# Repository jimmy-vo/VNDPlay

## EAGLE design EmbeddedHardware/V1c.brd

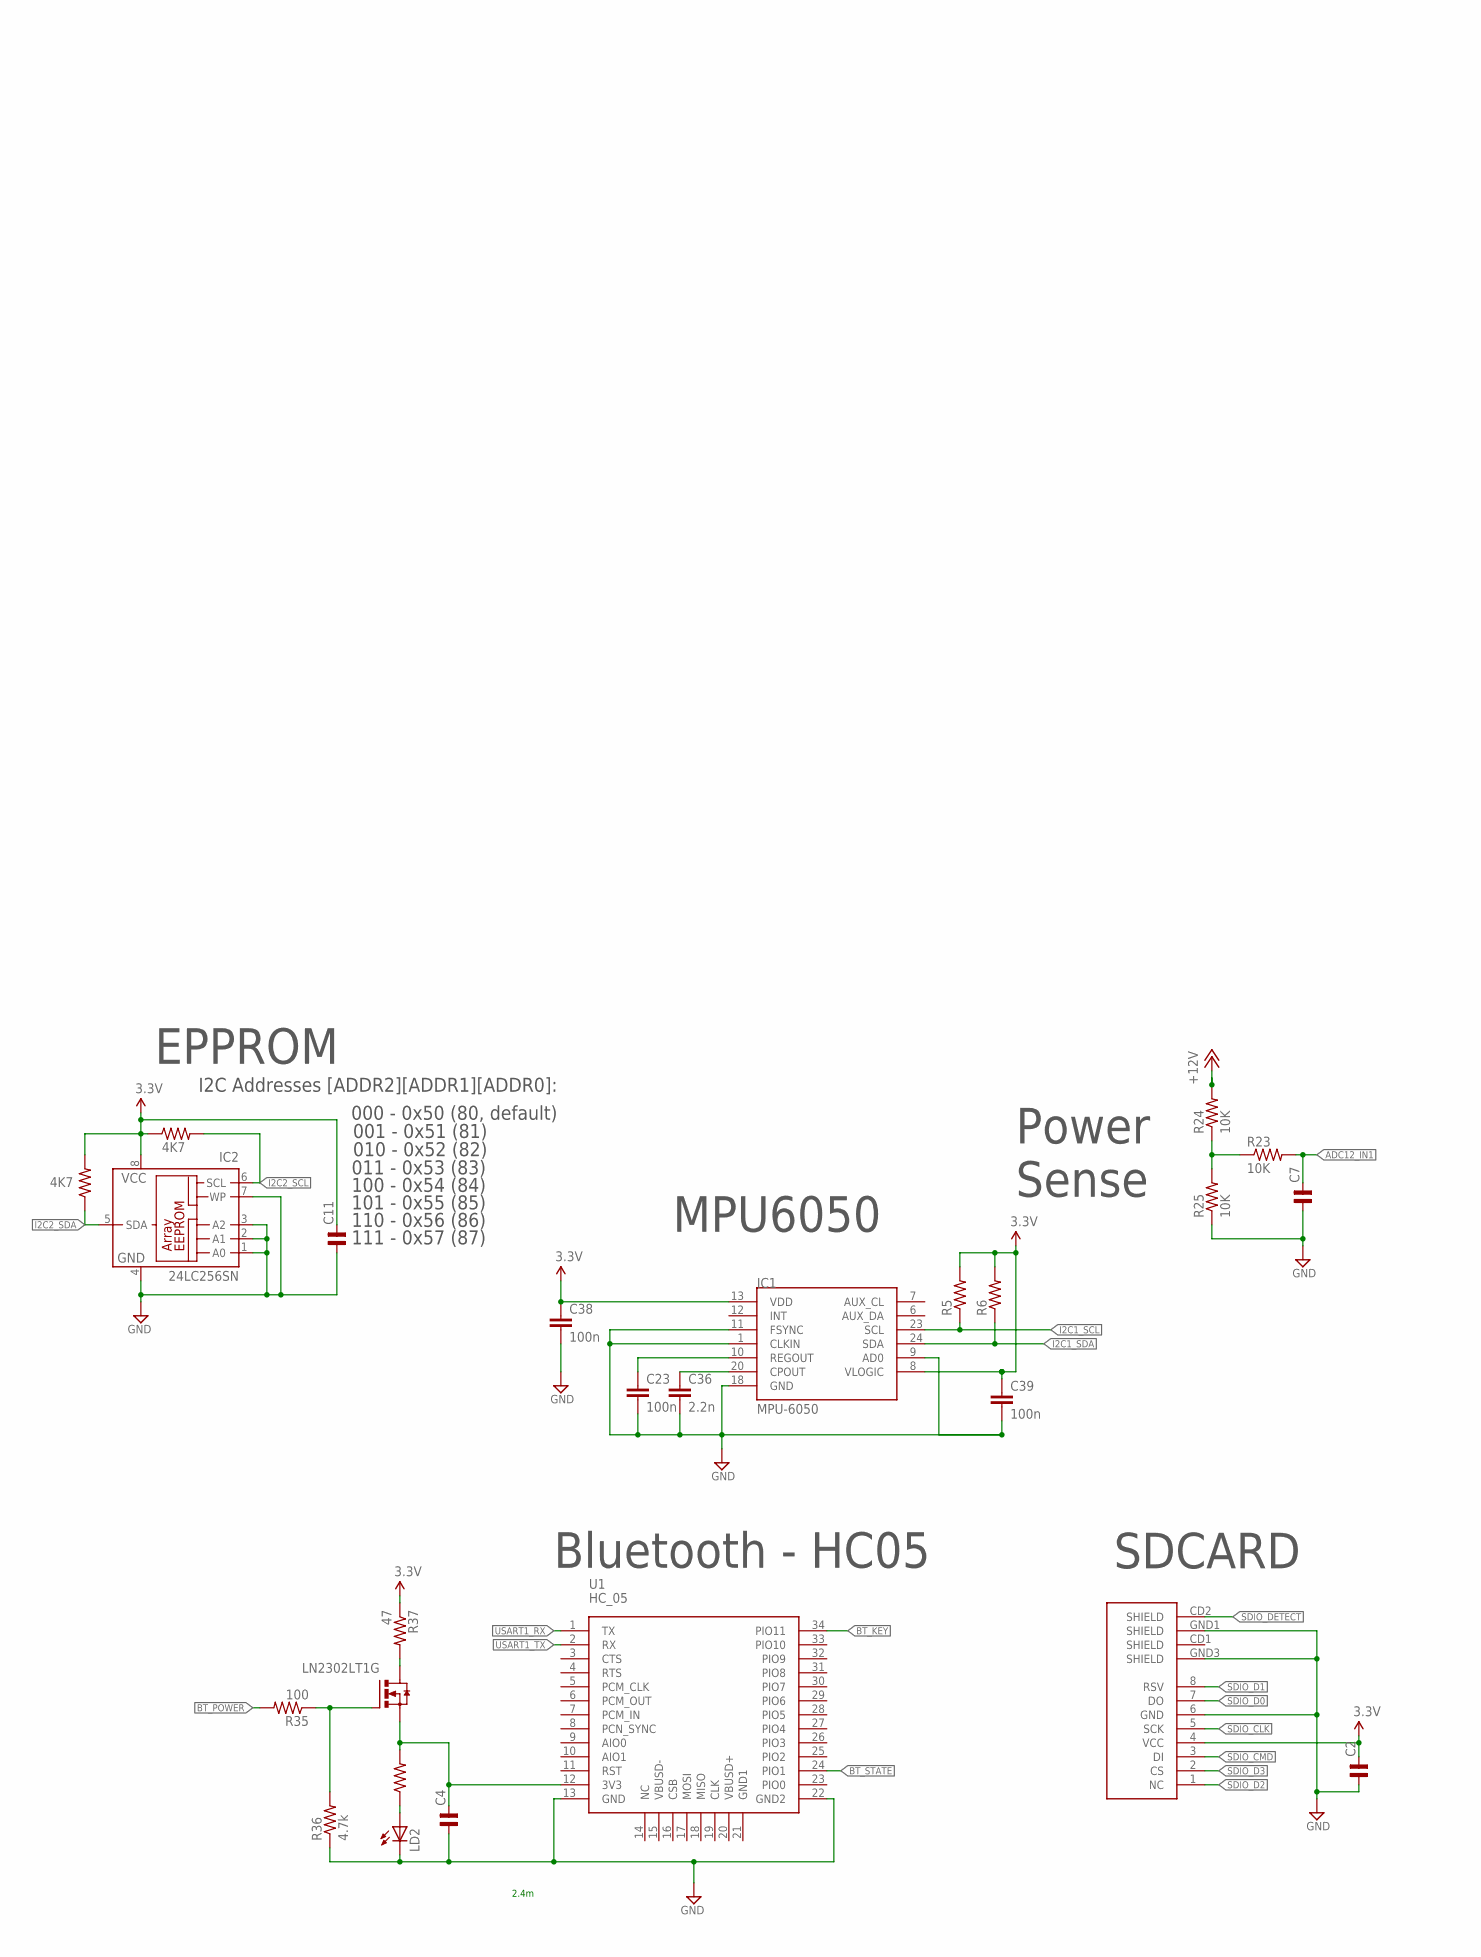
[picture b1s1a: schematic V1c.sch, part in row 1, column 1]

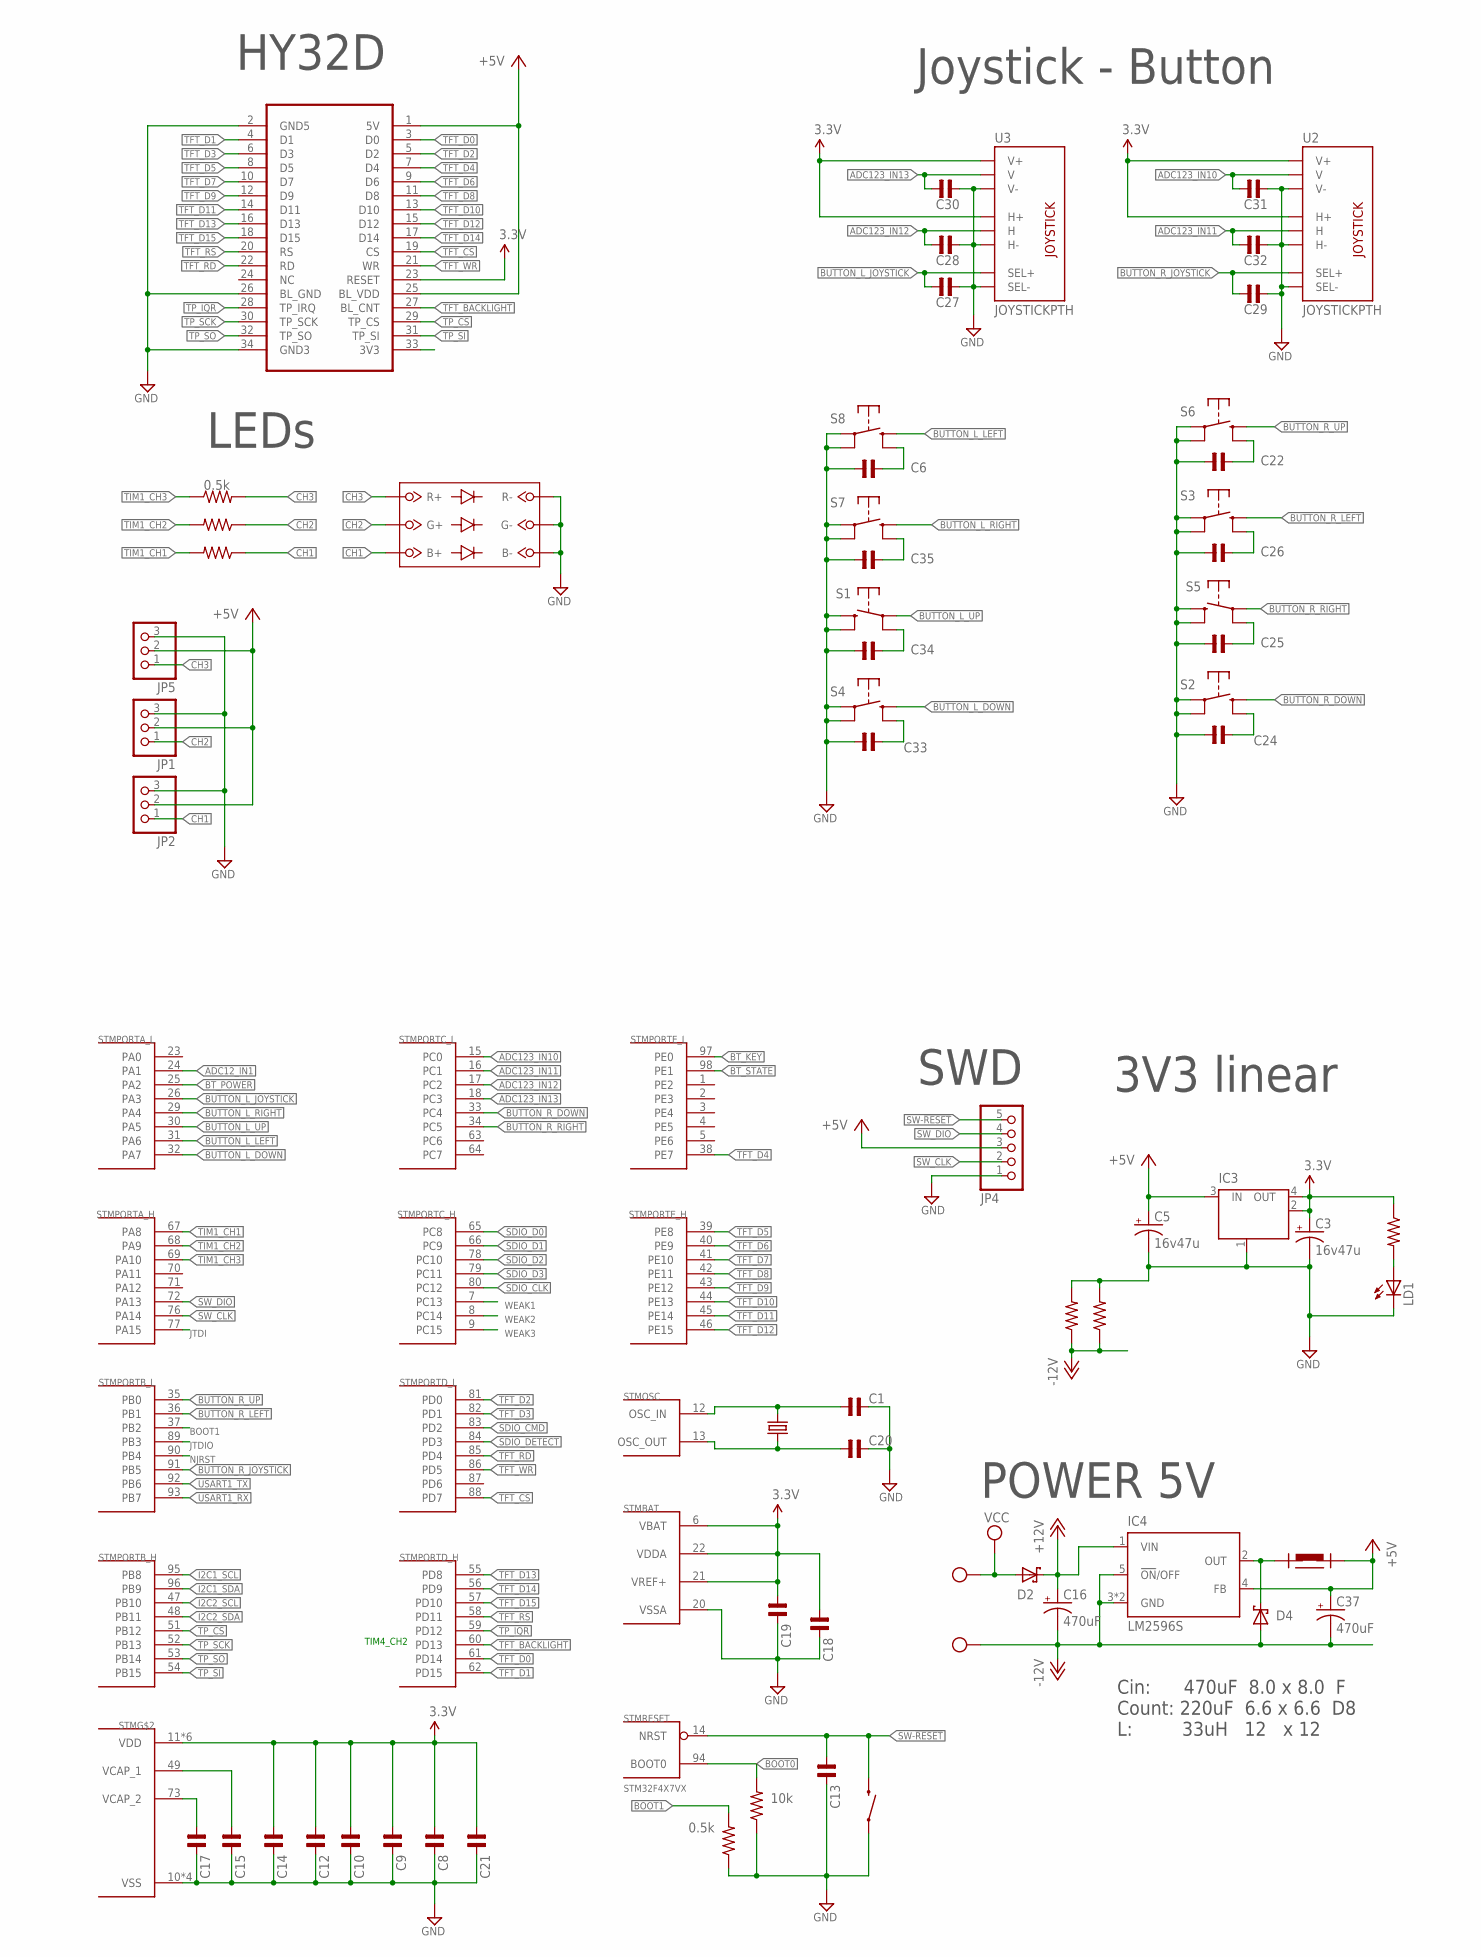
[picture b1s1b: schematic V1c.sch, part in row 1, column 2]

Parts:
C1, C2, C4, C6, C7, C8, C9, C10, C11, C12, C13, C14, C15, C17, C18, C19, C20, C21, C22, C24, C25, C26, C27, C28, C29, C30, C31, C32, C33, C34, C35: C-NP-SMD-0603; C-0603
C3, C5: 16v47u; SMC_C
C16: 470uF; 175TMP-0808
C23, C38, C39: 100n; SPARKFUN_0603-CAP
C36: 2.2n; SPARKFUN_0603-CAP
C37: 470uF; E/7260-38W
D2, D4: MBRS330T3; SMC
IC1: MPU-6050; TESTING_QFN-24-4MM2
IC2: 24LC256SN; SO-08; DIGIKEY 24LC256-E/SN-ND
IC3: LINEAR_MC33269ST-3.3T3; LINEAR_SOT223
IC4: LM2596S; TO263-5
JP1, JP2, JP5: PINHD-1X3_2.54-90°; 1X03/90
JP4: PINHD-1X5_2.54-90°; 1X05/90
LD1, LD2: LEDCHIPLED_0805; CHIPLED_0805
LN2302LT1G: FDN327N; SOT-23
R1, R2, R7: 10k; SPARKFUN_0603-RES
R5, R6: SPARKFUN_RESISTOR0603-RES; SPARKFUN_0603-RES
R8: 0.5k; SPARKFUN_0603-RES
R9, R10, R11, R12, R23, R24, R25, R39: 10K; SPARKFUN_0603-RES
R15, R16: 4K7; SPARKFUN_0603-RES
R35: 100; SPARKFUN_0603-RES
R36: 4.7k; SPARKFUN_0603-RES
R37: 47; SPARKFUN_0603-RES
S1, S2, S3, S4, S5, S6, S7, S8: RACON12/
S9: RESET; TACTILE-SWITCH-1101NE; PARTNO EVQ-P7J01P
SDCARD2: microSD Socket; MICRO-SD-SOCKET-PP
STM: STM32F4X7VX; TQFP100; PARTNO STM32F427VI
U1: HC_05; BLUETOOTH_SMD
U2, U3: JOYSTICKPTH; JOYSTICK
U$3: TFT3.2; HY32D_2
U$5: BIG_INDUCTOR; 12X12
U$13: RGB_LED; SMD
X1: MKDSN1,5/2-5,08
Y1: CRYSTALHC49US; HC49US

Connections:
3.3V: C2.2, C3.+, C8.1, C9.1, C10.1, C11.2, C12.1, C14.1, C18.1, C19.1, C21.1, C38.1, C39.1, IC1.8 (VLOGIC), IC1.13 (VDD), IC2.8 (VCC), IC3.2 (OUT), IC3.4 (OUT), R5.2, R6.2, R9.1, R15.1, R16.2, R37.1, SDCARD2.4 (VCC), STM.6 (VBAT), STM.11 (VDD), STM.19 (VDD), STM.21 (VREF+), STM.22 (VDDA), STM.28 (VDD), STM.50 (VDD), STM.75 (VDD), STM.100 (VDD), U2.H1 (H+), U2.V1 (V+), U3.H1 (H+), U3.V1 (V+), U$3.23 (RESET)
+5V: C5.+, C37.+, IC3.3 (IN), IC4.4 (FB), JP1.2, JP2.2, JP4.3, JP5.2, U$3.1 (5V), U$3.25 (BL_VDD), U$5.P$1
+12V: C16.+, D2.C, IC4.1 (VIN), R24.2
-12V: C16.-, C37.-, D4.A, IC4.3 (GND), IC4.5 (!ON!/OFF), IC4.6 (GND), R1.1, R2.1, X1.1
ADC12_IN1: C7.2, R23.2, STM.24 (PA1)
ADC123_IN10: C31.1, STM.15 (PC0), U2.V2 (V)
ADC123_IN11: C32.1, STM.16 (PC1), U2.H2 (H)
ADC123_IN12: C28.1, STM.17 (PC2), U3.H2 (H)
ADC123_IN13: C30.1, STM.18 (PC3), U3.V2 (V)
BOOT0: R7.2, STM.94 (BOOT0)
BOOT1: R8.2, STM.37 (PB2)
BT_KEY: STM.97 (PE0), U1.34 (PIO11)
BT_POWER: R35.2, STM.25 (PA2)
BT_STATE: STM.98 (PE1), U1.24 (PIO1)
BUTTON_L_DOWN: S4.1 (S), STM.32 (PA7)
BUTTON_L_JOYSTICK: C27.1, STM.26 (PA3), U3.B1A (SEL+)
BUTTON_L_LEFT: S8.1 (S), STM.31 (PA6)
BUTTON_L_RIGHT: S7.1 (S), STM.29 (PA4)
BUTTON_L_UP: S1.3, STM.30 (PA5)
BUTTON_R_DOWN: S2.1 (S), STM.33 (PC4)
BUTTON_R_JOYSTICK: C29.1, STM.91 (PB5), U2.B1A (SEL+)
BUTTON_R_LEFT: S3.1 (S), STM.36 (PB1)
BUTTON_R_RIGHT: S5.3, STM.34 (PC5)
BUTTON_R_UP: S6.1 (S), STM.35 (PB0)
CH1: JP2.1, R11.1, U$13.B+
CH2: JP1.1, R39.1, U$13.G+
CH3: JP5.1, R12.2, U$13.R+
GND: C1.2, C2.1, C3.-, C4.1, C5.-, C6.1, C7.1, C8.2, C9.2, C10.2, C11.1, C12.2, C13.2, C14.2, C15.2, C17.2, C18.2, C19.2, C20.2, C21.2, C22.1, C23.2, C24.2, C25.2, C26.2, C27.2, C28.2, C29.2, C30.2, C31.2, C32.2, C33.2, C34.2, C35.2, C36.2, C38.2, C39.2, IC1.1 (CLKIN), IC1.9 (AD0), IC1.11 (FSYNC), IC1.18 (GND), IC2.1 (A0), IC2.2 (A1), IC2.3 (A2), IC2.4 (GND), IC2.7 (WP), IC3.1 (GND/ADJ), JP1.3, JP2.3, JP4.1, JP5.3, LD1.C, LD2.C, R1.2, R2.2, R7.1, R8.1, R25.1, R36.1, S1.1 (S), S1.2 (S), S2.3, S2.4, S3.3, S3.4, S4.3, S4.4, S5.1 (S), S5.2 (S), S6.3, S6.4, S7.3, S7.4, S8.3, S8.4, S9.P$1 (1), SDCARD2.6 (GND), SDCARD2.GND1 (SHIELD), SDCARD2.GND3 (SHIELD), STM.10 (VSS), STM.20 (VSSA), STM.27 (VSS), STM.74 (VSS), STM.99 (VSS), U1.13 (GND), U1.22 (GND2), U2.B2A (SEL-), U2.H3 (H-), U2.V3 (V-), U3.B2A (SEL-), U3.H3 (H-), U3.V3 (V-), U$3.2 (GND5), U$3.26 (BL_GND), U$3.34 (GND3), U$13.B-, U$13.G-, U$13.R-
I2C1_SCL: IC1.23 (SCL), R5.1, STM.95 (PB8)
I2C1_SDA: IC1.24 (SDA), R6.1, STM.96 (PB9)
I2C2_SCL: IC2.6 (SCL), R15.2, STM.47 (PB10)
I2C2_SDA: IC2.5 (SDA), R16.1, STM.48 (PB11)
JTDI: STM.77 (PA15)
JTDIO: STM.89 (PB3)
unnamed: C1.1, STM.12 (OSC_IN), Y1.2
unnamed: C6.2, S8.2 (S)
unnamed: C23.1, IC1.10 (REGOUT)
unnamed: C36.1, IC1.20 (CPOUT)
unnamed: C22.2, S6.2 (S)
unnamed: C35.1, S7.2 (S)
unnamed: C25.1, S5.4
unnamed: C4.2, LN2302LT1G.2 (S), R10.2, U1.12 (3V3)
unnamed: C24.1, S2.2 (S)
unnamed: C26.1, S3.2 (S)
unnamed: LN2302LT1G.3 (D), R37.2
unnamed: C34.1, S1.4
unnamed: C33.1, S4.2 (S)
unnamed: LD1.A, R9.2
unnamed: LD2.A, R10.1
unnamed: R23.1, R24.1, R25.2
unnamed: C20.1, STM.13 (OSC_OUT), Y1.1
unnamed: C17.1, STM.73 (VCAP_2)
unnamed: C15.1, STM.49 (VCAP_1)
unnamed: LN2302LT1G.1 (G), R35.1, R36.2
NJRST: STM.90 (PB4)
OUT1: D4.C, IC4.2 (OUT), U$5.P$2
SDIO_CLK: SDCARD2.5 (SCK), STM.80 (PC12)
SDIO_CMD: SDCARD2.3 (DI), STM.83 (PD2)
SDIO_D0: SDCARD2.7 (DO), STM.65 (PC8)
SDIO_D1: SDCARD2.8 (RSV), STM.66 (PC9)
SDIO_D2: SDCARD2.1 (NC), STM.78 (PC10)
SDIO_D3: SDCARD2.2 (CS), STM.79 (PC11)
SDIO_DETECT: SDCARD2.CD2 (SHIELD), STM.84 (PD3)
SW-!RESET: C13.1, JP4.5, S9.P$2 (2), STM.14 (NRST)
SW_CLK: JP4.2, STM.76 (PA14)
SW_DIO: JP4.4, STM.72 (PA13)
TFT_BACKLIGHT: STM.60 (PD13), U$3.27 (BL_CNT)
TFT_CS: STM.88 (PD7), U$3.19 (CS)
TFT_D0: STM.61 (PD14), U$3.3 (D0)
TFT_D1: STM.62 (PD15), U$3.4 (D1)
TFT_D2: STM.81 (PD0), U$3.5 (D2)
TFT_D3: STM.82 (PD1), U$3.6 (D3)
TFT_D4: STM.38 (PE7), U$3.7 (D4)
TFT_D5: STM.39 (PE8), U$3.8 (D5)
TFT_D6: STM.40 (PE9), U$3.9 (D6)
TFT_D7: STM.41 (PE10), U$3.10 (D7)
TFT_D8: STM.42 (PE11), U$3.11 (D8)
TFT_D9: STM.43 (PE12), U$3.12 (D9)
TFT_D10: STM.44 (PE13), U$3.13 (D10)
TFT_D11: STM.45 (PE14), U$3.14 (D11)
TFT_D12: STM.46 (PE15), U$3.15 (D12)
TFT_D13: STM.55 (PD8), U$3.16 (D13)
TFT_D14: STM.56 (PD9), U$3.17 (D14)
TFT_D15: STM.57 (PD10), U$3.18 (D15)
TFT_RD: STM.85 (PD4), U$3.22 (RD)
TFT_RS: STM.58 (PD11), U$3.20 (RS)
TFT_WR: STM.86 (PD5), U$3.21 (WR)
TIM1_CH1: R11.2, STM.67 (PA8)
TIM1_CH2: R39.2, STM.68 (PA9)
TIM1_CH3: R12.1, STM.69 (PA10)
TP_CS: STM.51 (PB12), U$3.29 (TP_CS)
TP_IQR: STM.59 (PD12), U$3.28 (TP_IRQ)
TP_SCK: STM.52 (PB13), U$3.30 (TP_SCK)
TP_SI: STM.54 (PB15), U$3.31 (TP_SI)
TP_SO: STM.53 (PB14), U$3.32 (TP_SO)
USART1_RX: STM.93 (PB7), U1.1 (TX)
USART1_TX: STM.92 (PB6), U1.2 (RX)
VCC: D2.A, X1.2
WEAK1: STM.7 (PC13)
WEAK2: STM.8 (PC14)
WEAK3: STM.9 (PC15)

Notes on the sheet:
SWD
TIM4_CH2
I2C Addresses [ADDR2][ADDR1][ADDR0]:
000 - 0x50 (80, default)
001 - 0x51 (81)
010 - 0x52 (82)
011 - 0x53 (83)
100 - 0x54 (84)
101 - 0x55 (85)
110 - 0x56 (86)
111 - 0x57 (87)
EPPROM
Bluetooth - HC05
SDCARD
Power Sense
3V3 linear
2.4m
POWER 5V
Cin: 470uF 8.0 x 8.0 F Count: 220uF 6.6 x 6.6 D8 L: 33uH 12 x 12
LEDs
MPU6050
HY32D
Joystick - Button

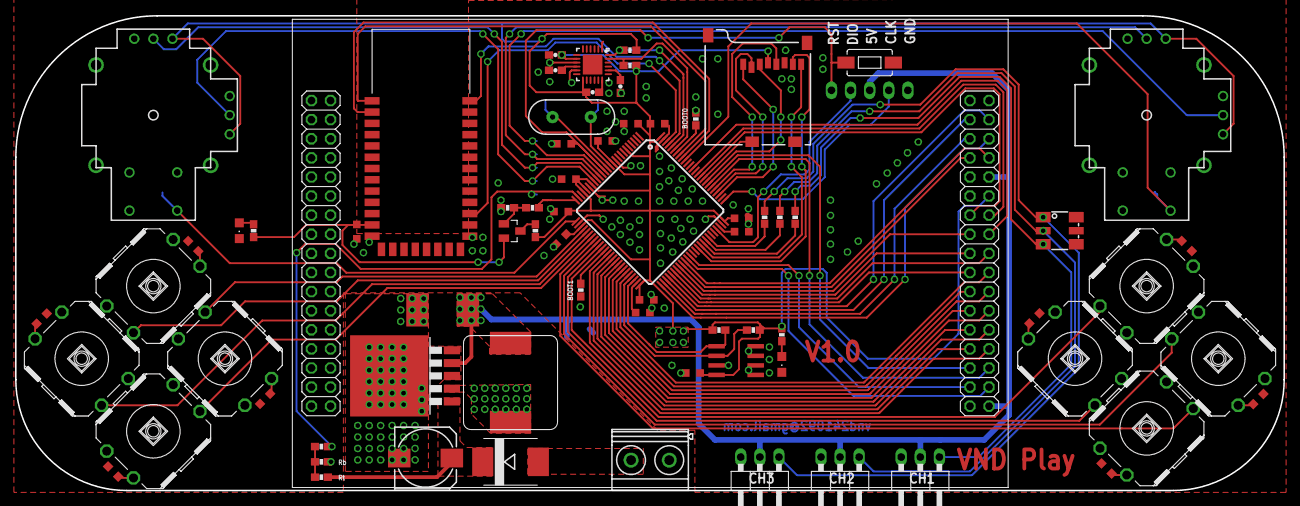
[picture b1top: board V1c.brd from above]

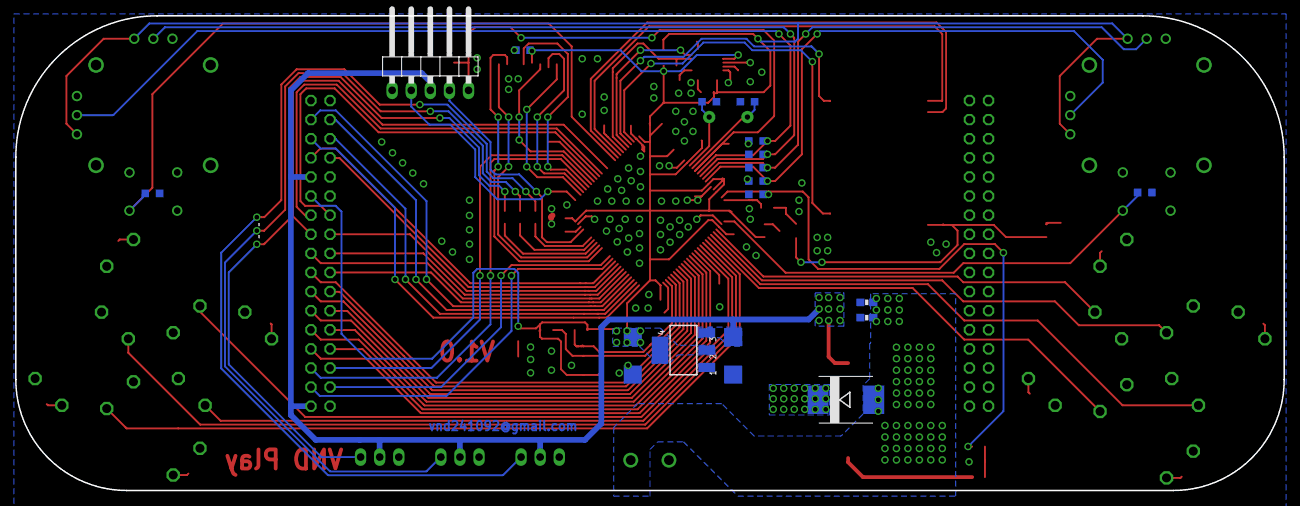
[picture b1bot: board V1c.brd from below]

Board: 2 copper layers, 168.7 x 63.1 mm, 90 parts (17 on the bottom side), 95 nets.

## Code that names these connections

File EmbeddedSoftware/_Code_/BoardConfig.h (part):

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#define I2C1_GPIO_CLK						RCC_AHB1Periph_GPIOB
#define I2C1_AF									GPIO_AF_I2C1

#define I2C1_SCL_PIN						GPIO_Pin_8
#define I2C1_SCL_SOURCE					GPIO_PinSource8
#define I2C1_SDA_PIN						GPIO_Pin_9
#define I2C1_SDA_SOURCE					GPIO_PinSource9

#define I2C1_RX_DMA_CH					DMA_Channel_1
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#define I2C2_GPIO_CLK						RCC_AHB1Periph_GPIOB
#define I2C2_AF									GPIO_AF_I2C2

#define I2C2_SCL_PIN						GPIO_Pin_10
#define I2C2_SCL_SOURCE					GPIO_PinSource10
#define I2C2_SDA_PIN						GPIO_Pin_11
#define I2C2_SDA_SOURCE					GPIO_PinSource11

#define I2C2_RX_DMA_CH					DMA_Channel_7
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  /////////////////////////////////////////////////////////////////
 //														SD CARD														//									
/////////////////////////////////////////////////////////////////
#define SDIO_CLK								RCC_APB2Periph_SDIO

#define SDIO_GPIO_DETECT_PORT		GPIOB
#define SDIO_GPIO_DETECT_CLK		RCC_AHB1Periph_GPIOB
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
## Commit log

2018-03-03 upload

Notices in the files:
parts and their libraries:
SparkFun-FreqCtrl: Licensing: CC v3.0 Share-Alike You are welcome to use this library for commercial purposes.
cap-pan40: Copyright (C) 2004, Bob Starr
